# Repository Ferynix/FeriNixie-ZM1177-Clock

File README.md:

# FeriNixie ZM1177 Clock
 A compact nixie tube clock designed for six ZM1177s

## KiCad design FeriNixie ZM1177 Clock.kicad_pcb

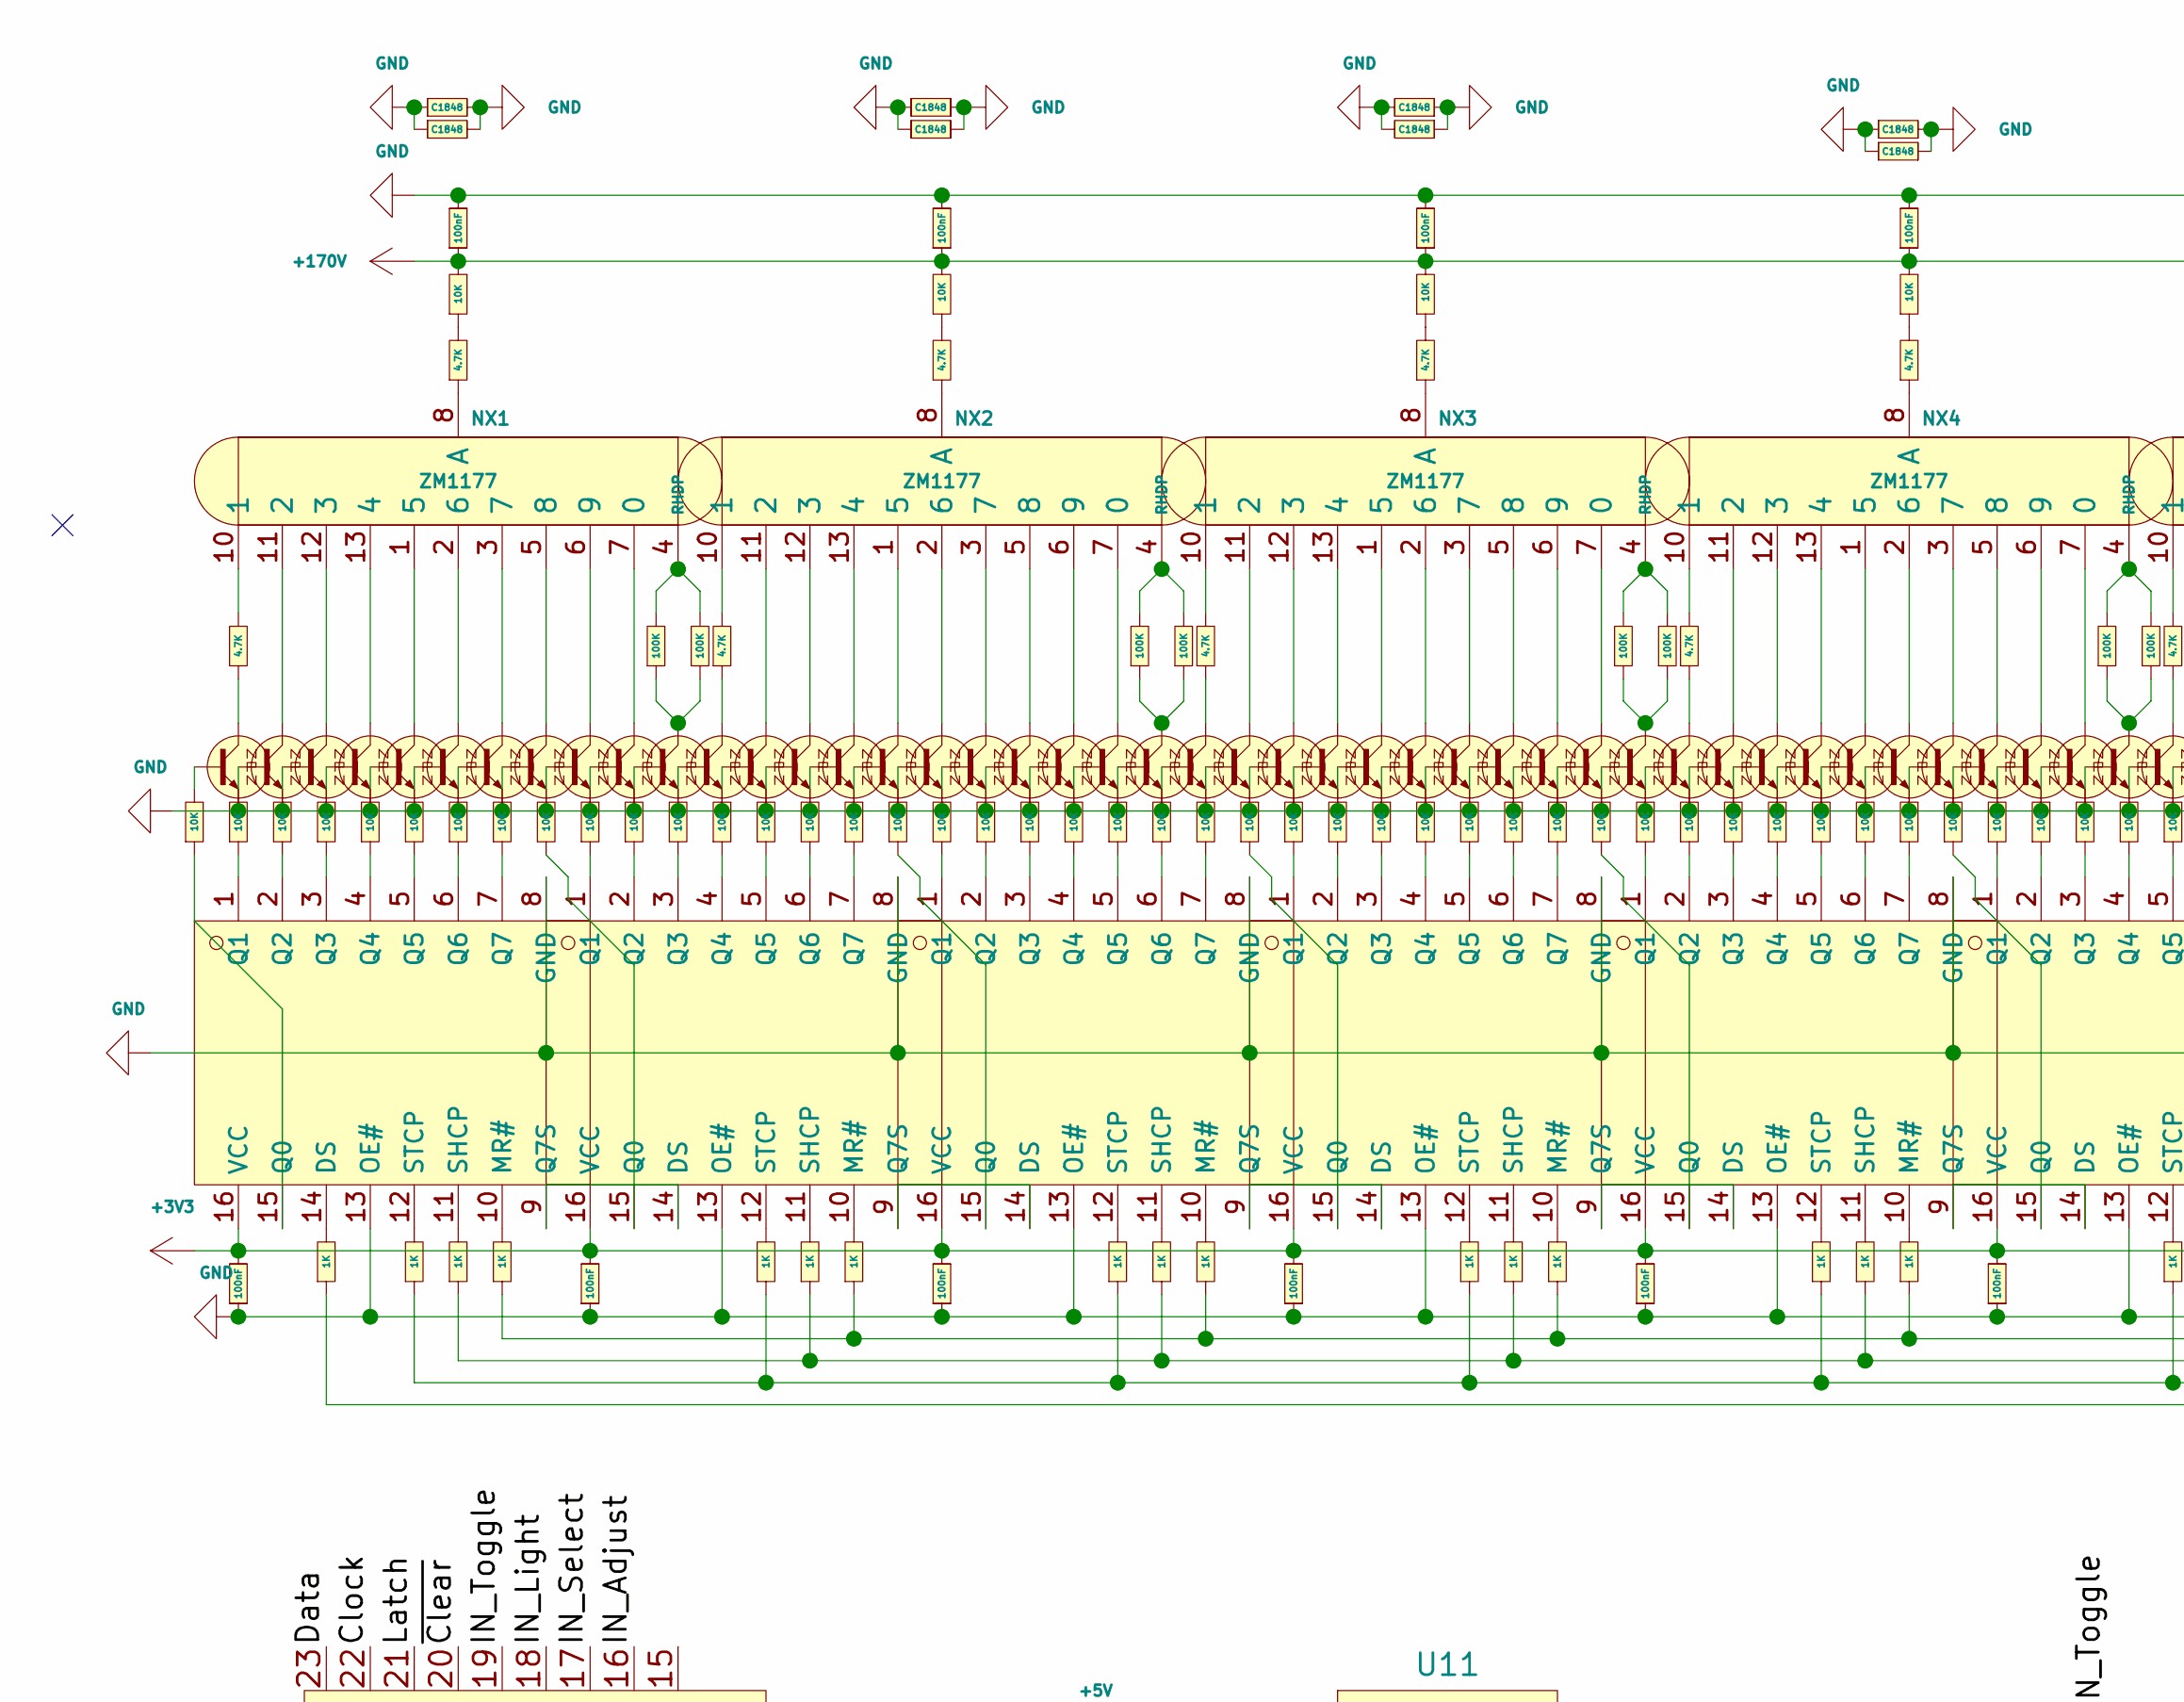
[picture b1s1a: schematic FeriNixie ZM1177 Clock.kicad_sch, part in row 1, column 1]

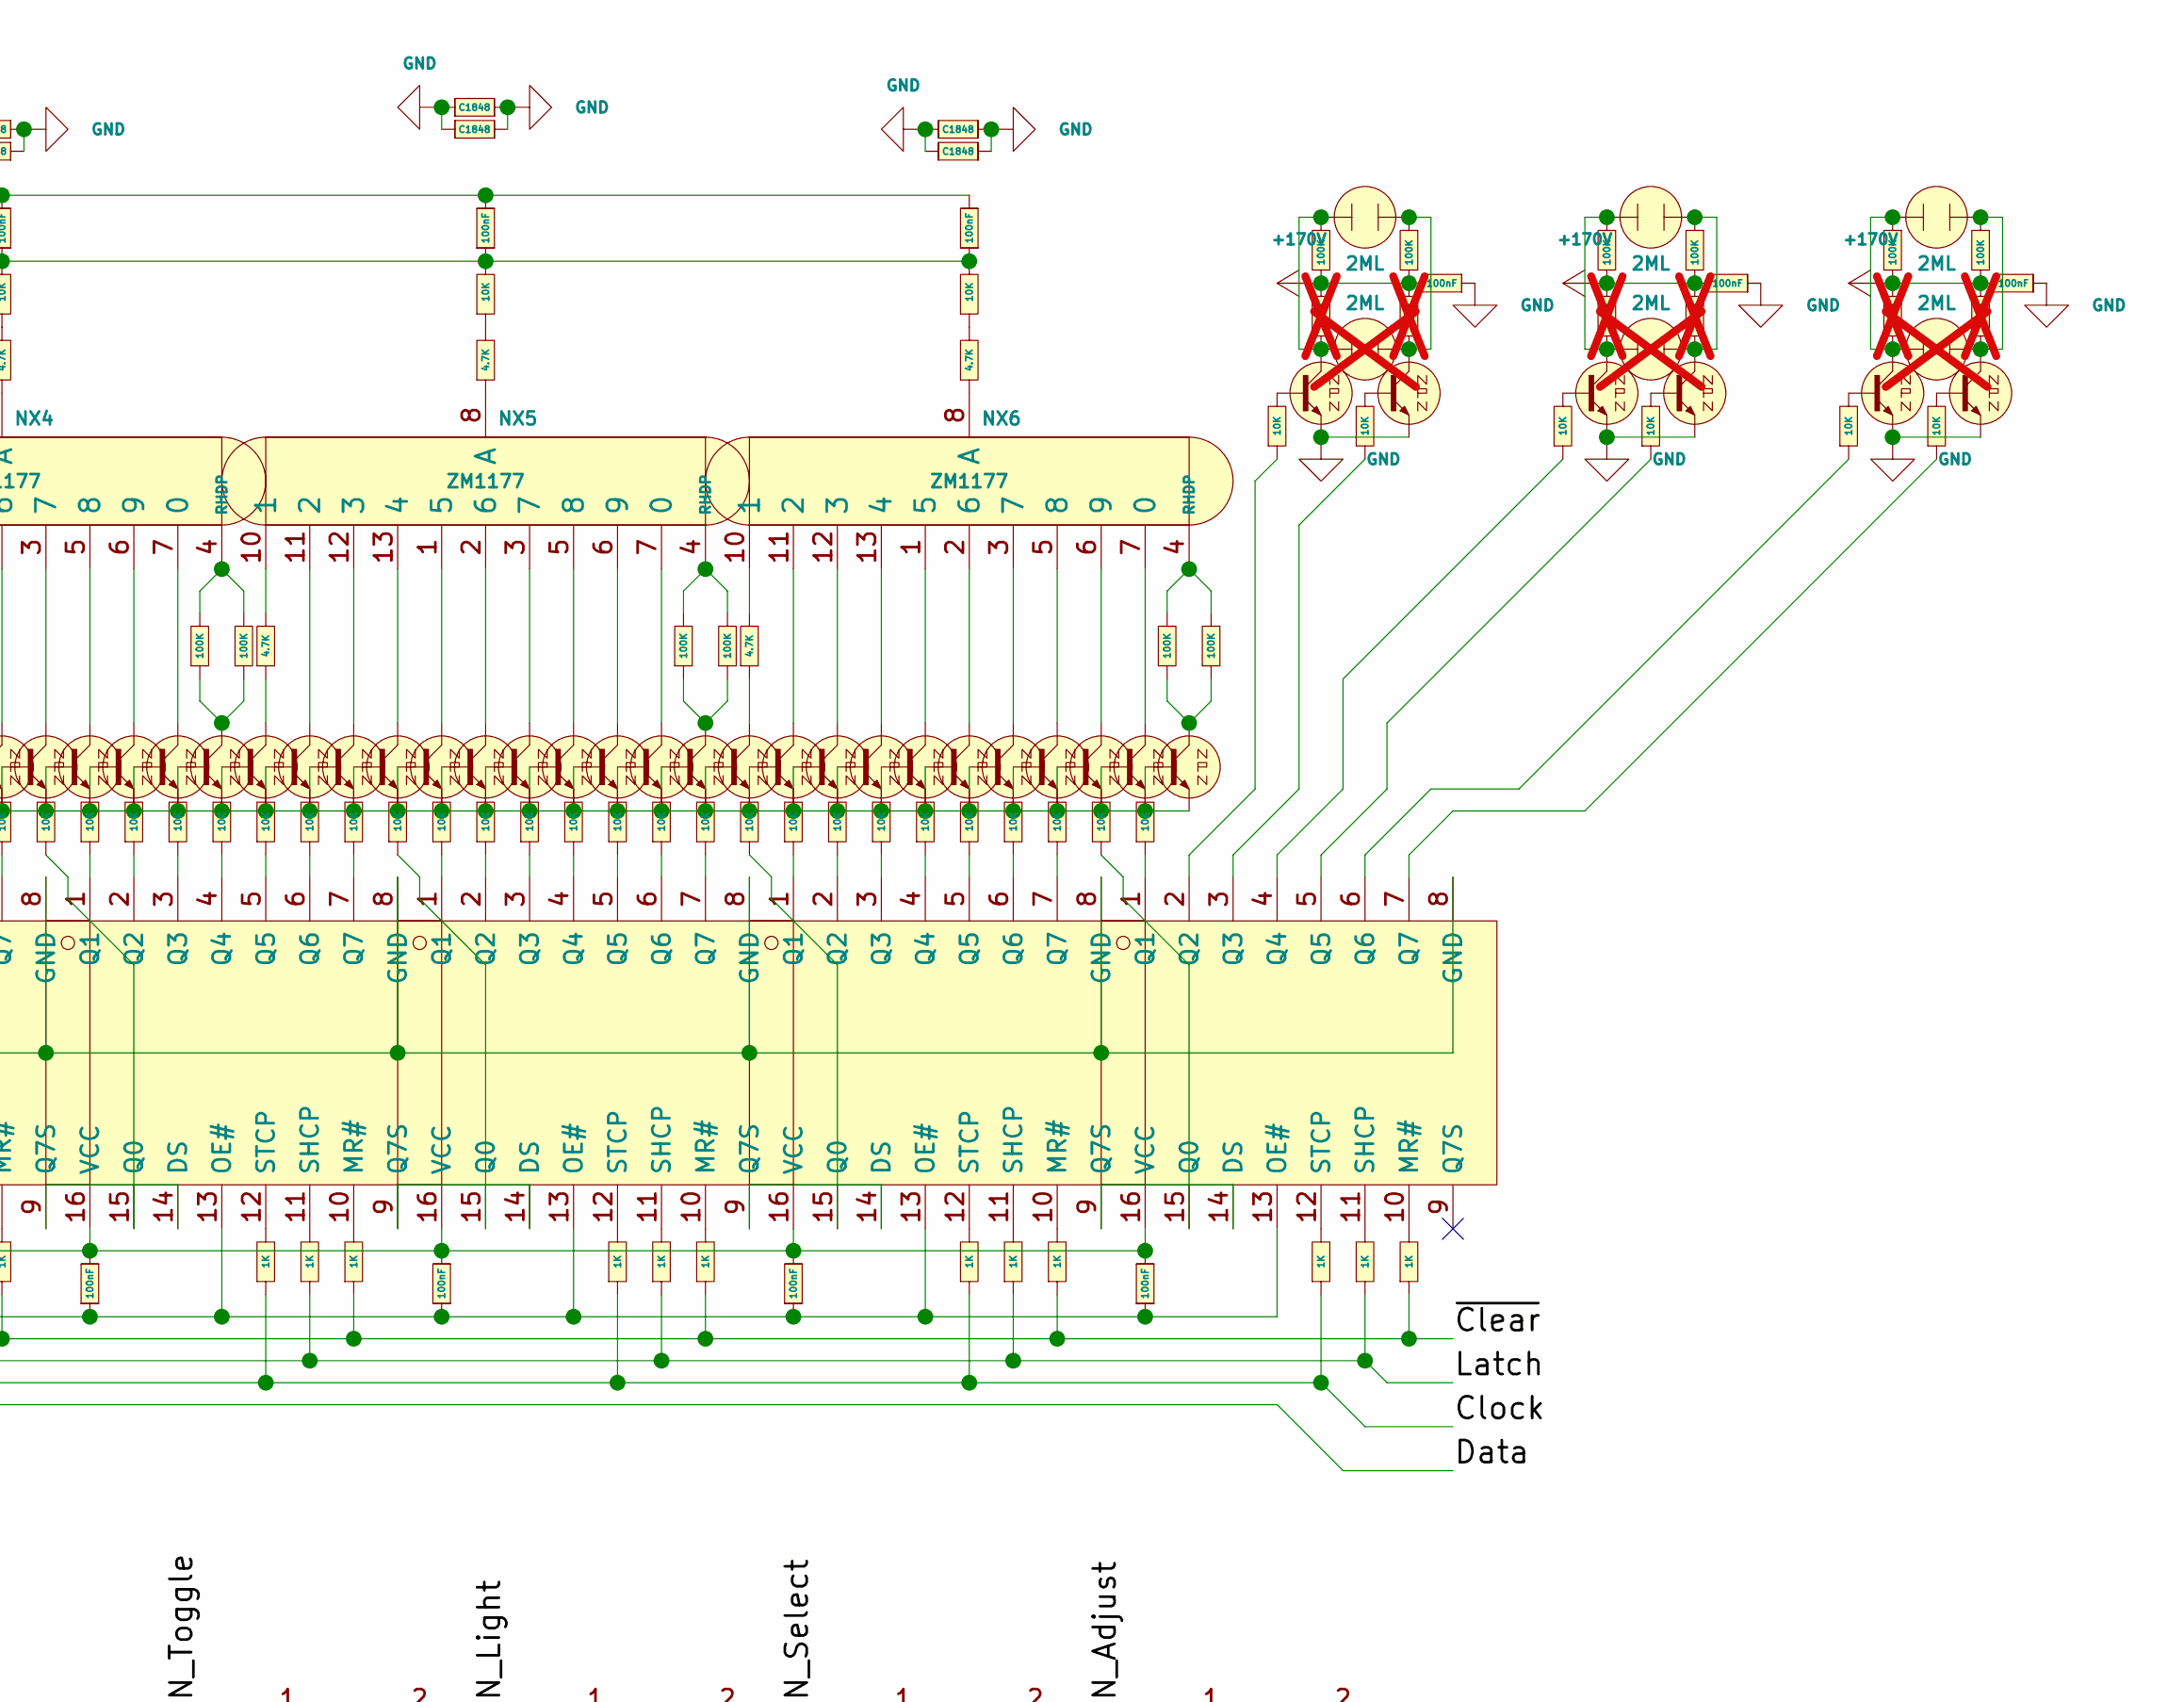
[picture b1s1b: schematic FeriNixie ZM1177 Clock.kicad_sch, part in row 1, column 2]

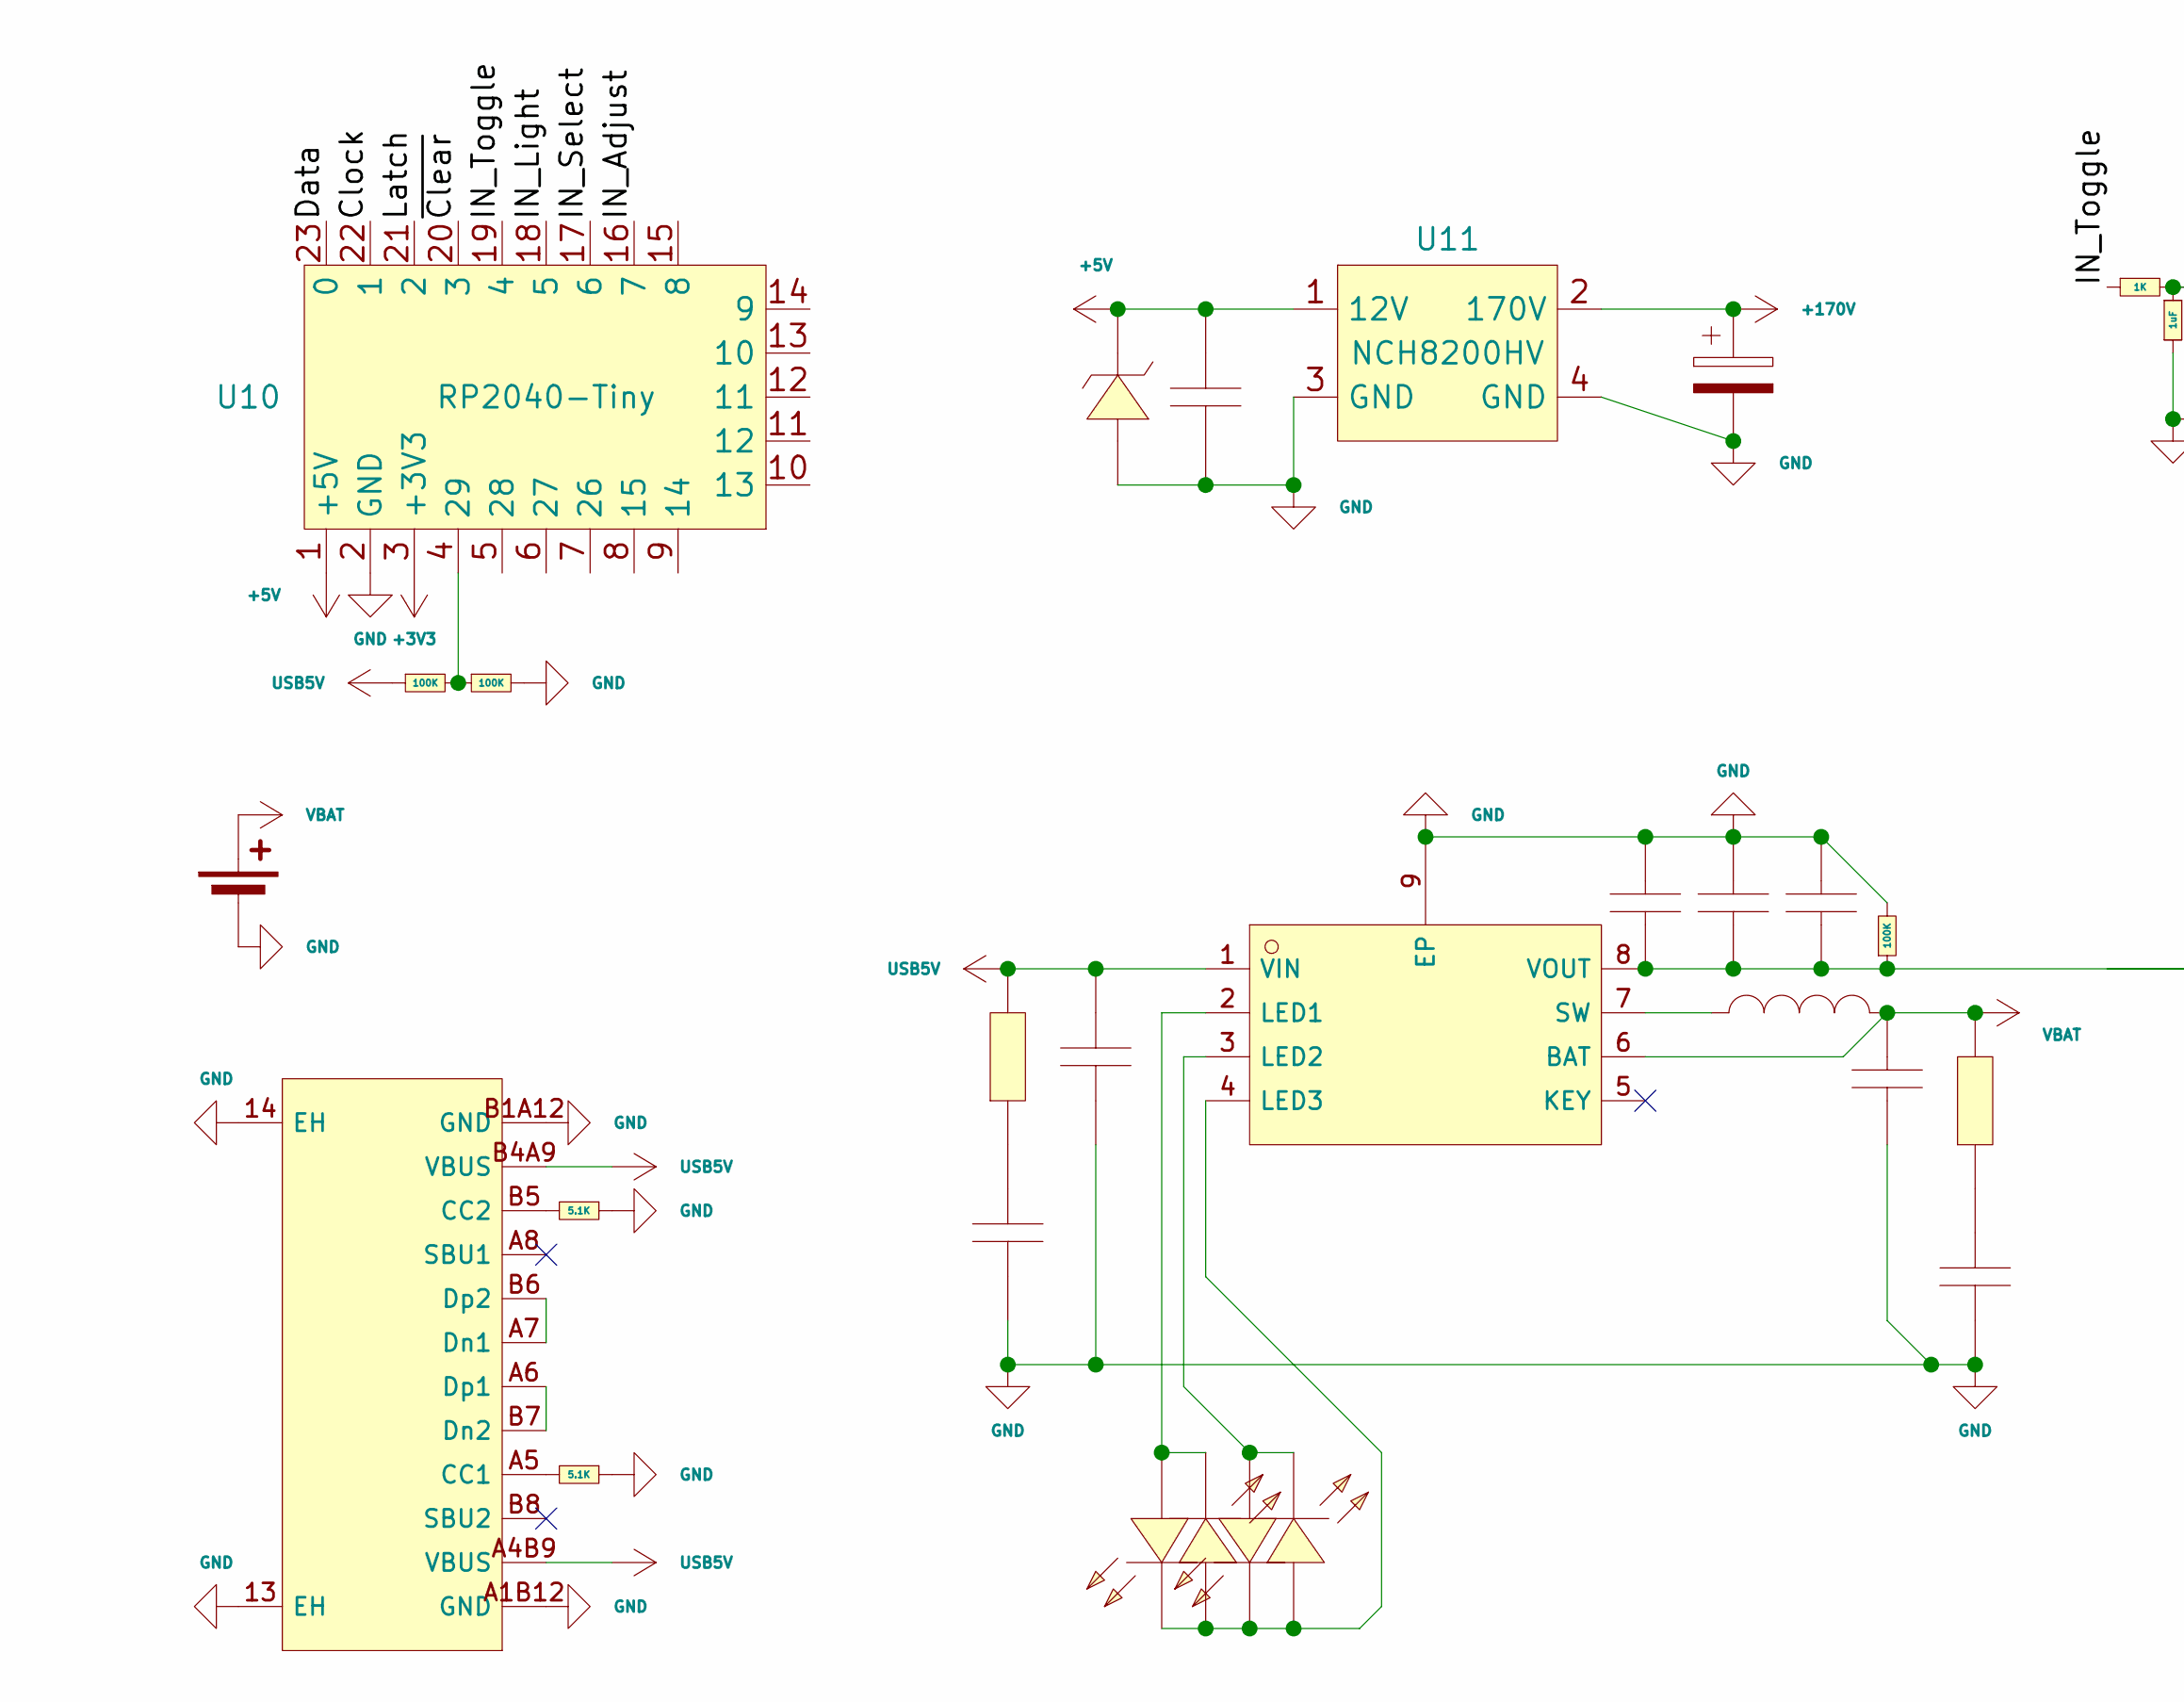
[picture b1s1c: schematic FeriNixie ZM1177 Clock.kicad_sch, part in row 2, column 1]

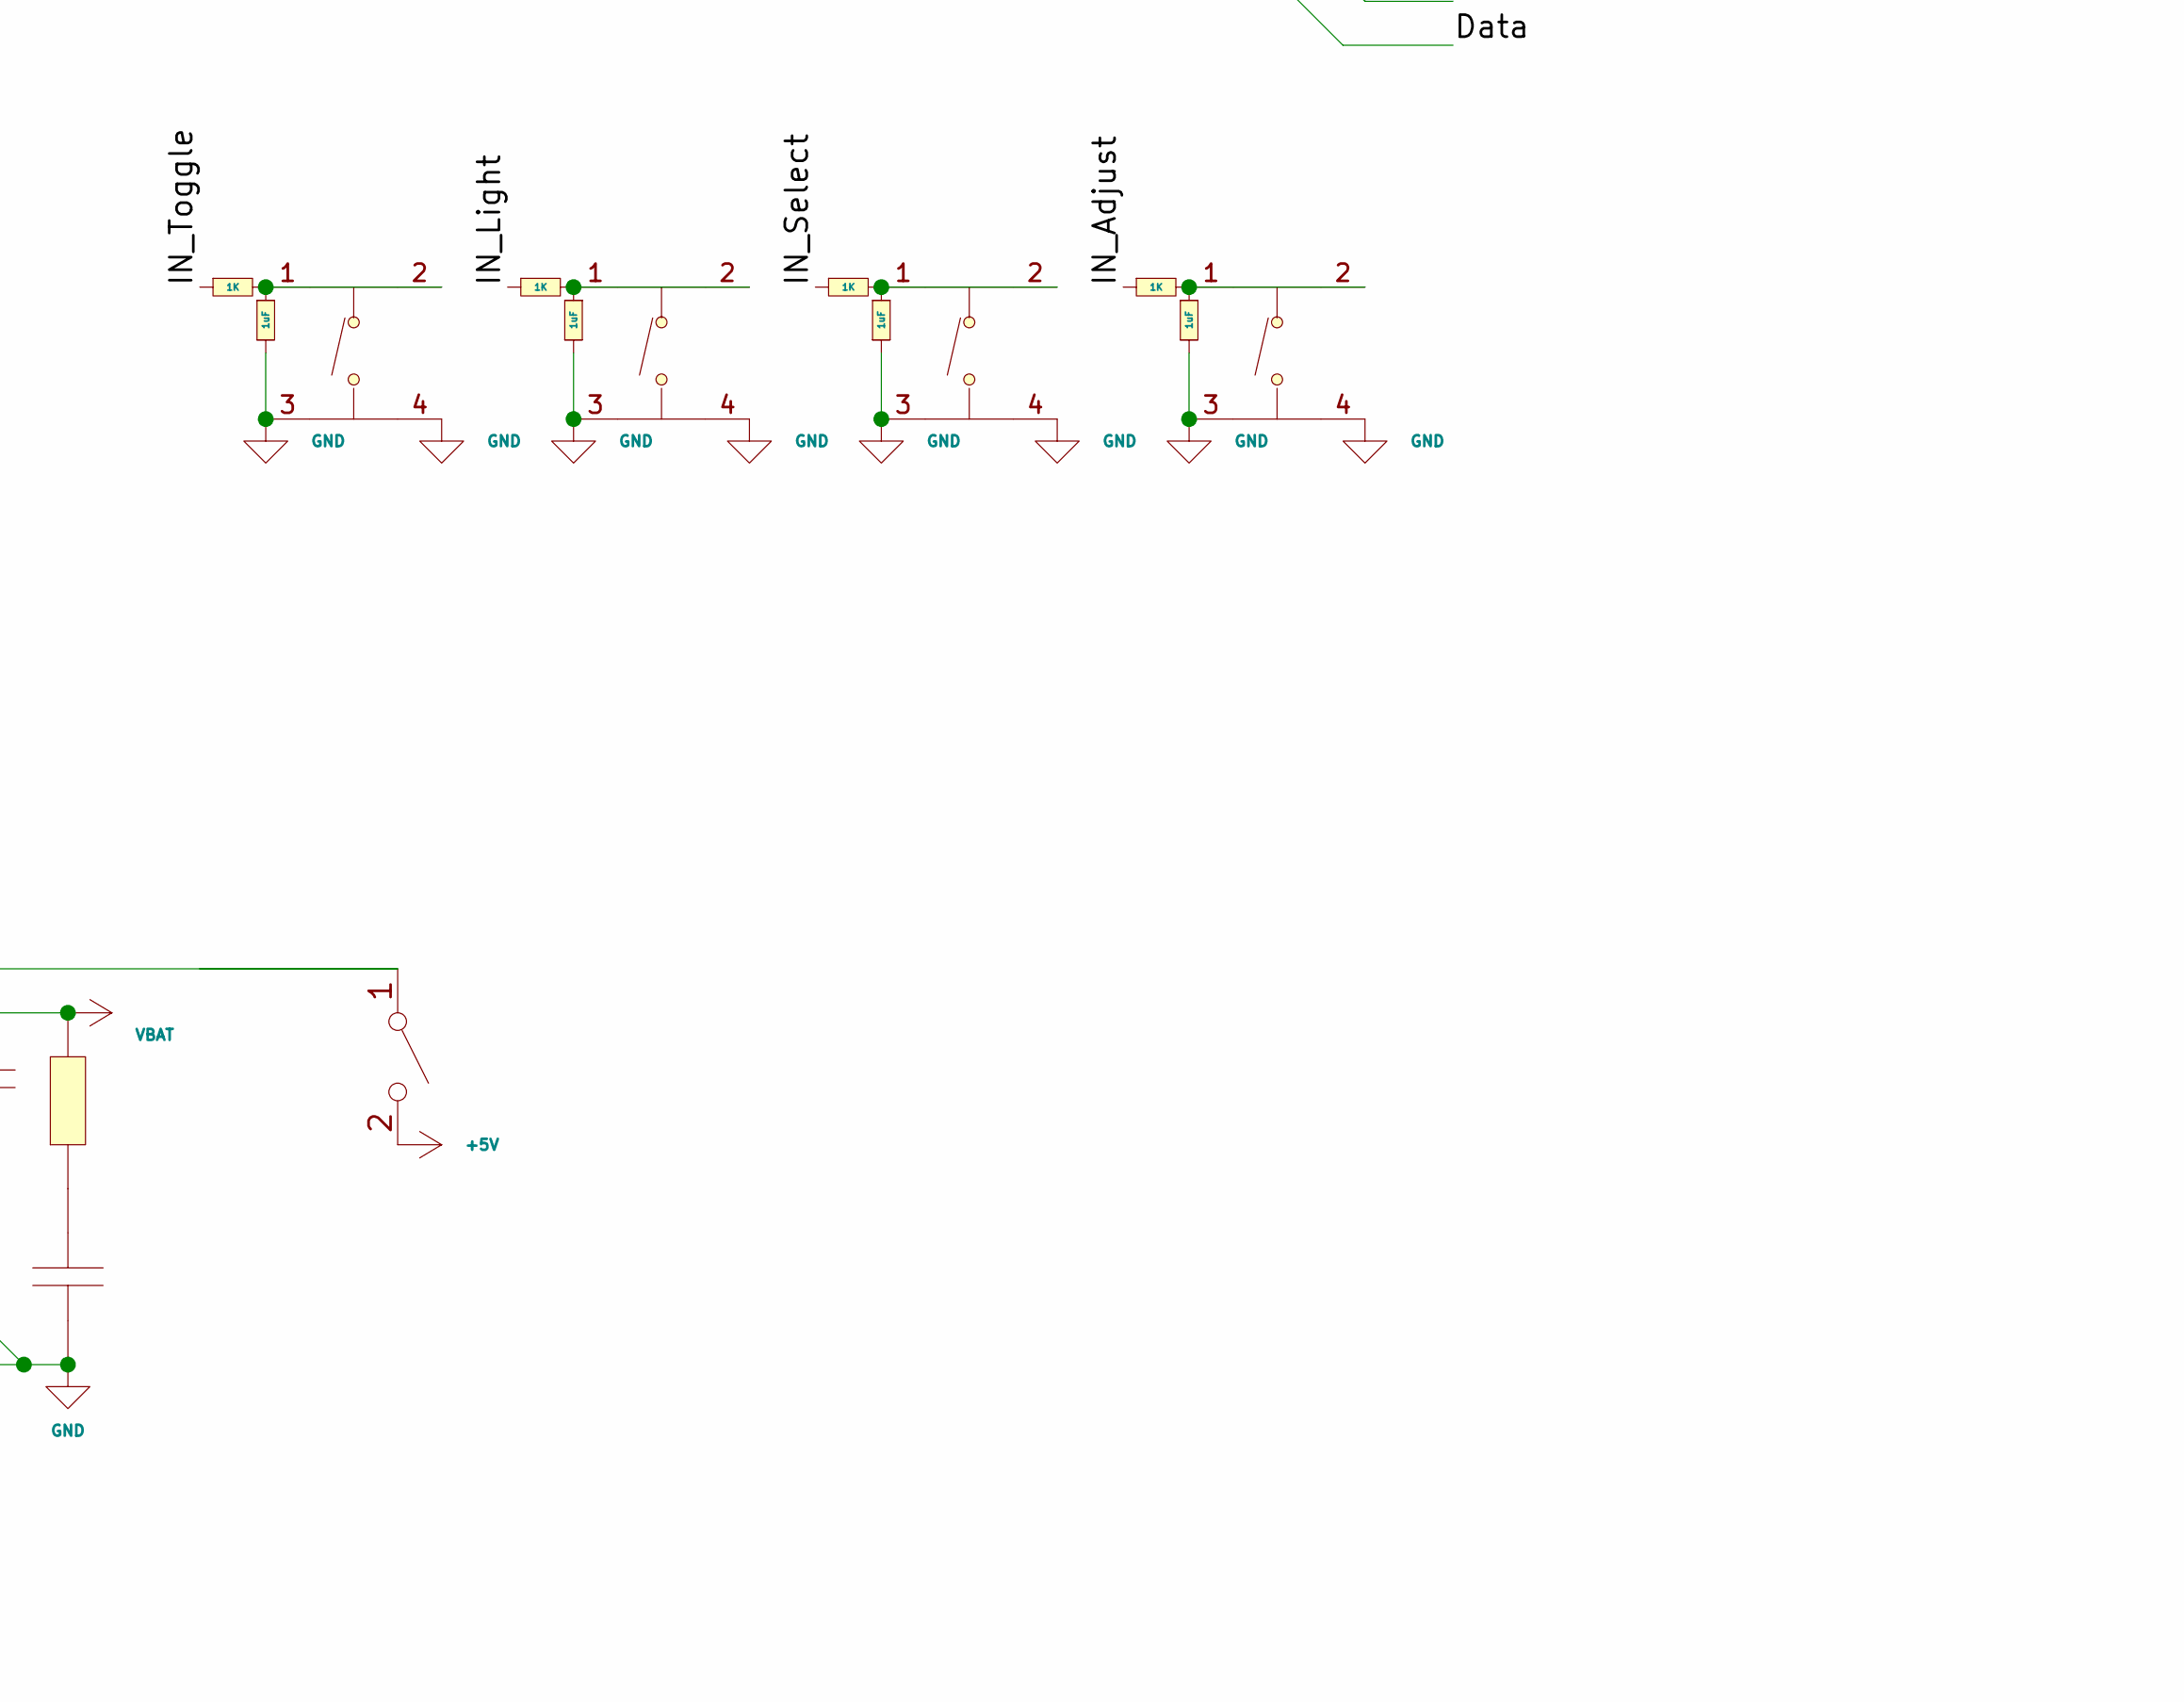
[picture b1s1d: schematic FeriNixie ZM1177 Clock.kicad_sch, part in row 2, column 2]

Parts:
BT1: Battery_Cell; BatteryHolder_Keystone_1042_1x18650
C1, C2, C3, C4, C5, C6, C7, C8, C43: 100nF; C_1206_3216Metric
C9, C10, C11, C12, C13, C14, C15, C16, C17: 100nF; C_0402_1005Metric
C18: C; C_Radial_D8.0mm_H11.5mm_P3.50mm
C19, C20, C21, C22, C23, C24, C25, C26, C27, C28, C29, C30: C1848
C31, C40, C41, C42: 1uF; R_0402_1005Metric
C32, C33, C37, C38: CL31A226KAHNNNE; C_1206_3216Metric; LCSC C12891
C34, C35, C36, C39: CL10A106KP8NNNC; C_0603_1608Metric; LCSC C19702
L1: FTM201610C1R0MCTA; L0806; LCSC C49211190
NE1, NE2, NE5: NeonIndicator_2ML_1MH_B10A
NE3, NE4, NE6: NeonIndicator_2ML_1MH_B10A; not fitted
NX1, NX2, NX3, NX4, NX5, NX6: NixieTube_ZM1177
Q1, Q2, Q3, Q4, Q5, Q6, Q7, Q8, Q9, Q10, Q11, Q12, Q13, Q14, Q15, Q16, Q17, Q18, Q19, Q20, Q21, Q22, Q23, Q24, Q25, Q26, Q27, Q28, Q29, Q30, Q31, Q32, Q33, Q34, Q35, Q36, Q37, Q38, Q39, Q40, Q41, Q42, Q43, Q44, Q45, Q46, Q47, Q48, Q49, Q50, Q51, Q52, Q53, Q54, Q55, Q56, Q57, Q58, Q59, Q60, Q61, Q62, Q63, Q64, Q65, Q66, Q67, Q68, Q69, Q70, Q71, Q72: C20069138; SOT-23-3_L2.9-W1.3-P1.90-LS2.4-BR
R1, R2, R3, R4, R5, R6: 10K; R_1206_3216Metric
R7, R9, R12, R14, R26, R27, R29, R30, R32, R33, R35, R36, R38, R39, R41, R42, R140, R146, R148, R150, R151: 100K; R_1206_3216Metric
R8, R10, R11, R13, R145, R149: 100K; R_1206_3216Metric; not fitted
R15, R16, R17, R18, R19, R20, R25, R28, R31, R34, R37, R40: 4.7K; R_1206_3216Metric
R21, R22, R23, R24, R43, R44, R45, R46, R47, R48, R49, R50, R51, R52, R53, R54, R55, R56, R57, R58, R59, R60, R61, R62, R63, R64, R65, R66, R67, R68, R69, R70, R71, R72, R73, R74, R75, R76, R77, R78, R79, R80, R81, R82, R83, R84, R85, R86, R87, R88, R89, R90, R91, R92, R93, R94, R95, R96, R97, R98, R99, R100, R101, R102, R103, R104, R105, R106, R107, R108, R137, R147: 10K; R_0402_1005Metric
R109, R110, R111, R112, R113, R114, R115, R116, R117, R118, R119, R120, R121, R122, R123, R124, R125, R126, R127, R128, R129, R130, R131, R132, R133, R134, R135, R136: 1K; R_0402_1005Metric
R138, R139: 0603WAF200KT5E; R_0603_1608Metric; LCSC C22977
R141, R142, R143, R144: 1K; C_0402_1005Metric
R254, R255: 5.1K; R_0402_1005Metric
SW1: SW_SPST; SW_SPST_L101011MS02Q
U1, U2, U3, U4, U5, U6, U7, U8, U9: 74HC595D,118; SOIC-16_L9.9-W3.9-P1.27-LS6.0-BL; LCSC C5947
U10: RP2040-Tiny; RP2040-Tiny Package Extra Clearance
U11: NCH8200HV; NCH8200HV Through-Hole
U12: 1SMA4740A_C19077479; SMA_L4.3-W2.6-LS5.0-RD; LCSC C19077479
U13: IP5306; ESOP-8_L4.9-W3.9-P1.27-LS6.0-BL-EP; LCSC C181692
U14: TYPE-C_16PIN_2MD(073); USB-C-SMD_TYPE-C-16PIN-2MD-073; LCSC C2765186
U15, U16, U17, U18: KT-0603R; LED-SMD_L1.6-W0.8-R-RD; LCSC C2286
U19, U20, U21, U22: TS-1187A-B-A-B; SW-SMD_4P-L5.1-W5.1-P3.70-LS6.5-TL_H1.5; LCSC C318884

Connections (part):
+3V3: C9.2, C10.2, C11.2, C12.2, C13.2, C14.2, C15.2, C16.2, C17.2, U1.16 (VCC), U2.16 (VCC), U3.16 (VCC), U4.16 (VCC), U5.16 (VCC), U6.16 (VCC), U7.16 (VCC), U8.16 (VCC), U9.16 (VCC), U10.3 (+3V3)
+5V: C39.2, SW1.2 (B), U10.1 (+5V), U11.1 (12V), U12.1 (K); also elsewhere on the board
+170V: C1.1, C2.1, C3.1, C4.1, C5.1, C6.1, C7.2, C8.2, C18.1, C43.2, R1.2, R2.2, R3.2, R4.2, R5.2, R6.2, R7.2, R8.2, R9.2, R10.2, R11.2, R12.2, R13.2, R14.2, R145.2, R146.2, R148.2, R149.2, U11.2 (170V)
/Clock: R110.1, R113.1, R116.1, R119.1, R122.1, R125.1, R128.1, R131.1, R134.1, U10.22 (1)
/Data: R109.1, U10.23 (0)
/IN_Adjust: R144.1, U10.16 (7)
/IN_Light: R142.1, U10.18 (5)
/IN_Select: R143.1, U10.17 (6)
/IN_Toggle: R141.1, U10.19 (4)
/Latch: R111.1, R114.1, R117.1, R120.1, R123.1, R126.1, R129.1, R132.1, R135.1, U10.21 (2)
/~Clear: R112.1, R115.1, R118.1, R121.1, R124.1, R127.1, R130.1, R133.1, R136.1, U10.20 (3)
GND: BT1.2 (-), C1.2, C2.2, C3.2, C4.2, C5.2, C6.2, C7.1, C8.1, C9.1, C10.1, C11.1, C12.1, C13.1, C14.1, C15.1, C16.1, C17.1, C18.2, C19.1, C19.2, C20.1, C20.2, C21.1, C21.2, C22.1, C22.2, C23.1, C23.2, C24.1, C24.2, C25.1, C25.2, C26.1, C26.2, C27.1, C27.2, C28.1, C28.2, C29.1, C29.2, C30.1, C30.2, C31.1, C32.1, C33.1, C34.1, C35.1, C36.1, C37.1, C38.1, C39.1, C40.1, C41.1, C42.1, C43.1, Q1.2 (E), Q2.2 (E), Q3.2 (E), Q4.2 (E), Q5.2 (E), Q6.2 (E), Q7.2 (E), Q8.2 (E), Q9.2 (E), Q10.2 (E), Q11.2 (E), Q12.2 (E), Q13.2 (E), Q14.2 (E), Q15.2 (E), Q16.2 (E), Q17.2 (E), Q18.2 (E), Q19.2 (E), Q20.2 (E), Q21.2 (E), Q22.2 (E), Q23.2 (E), Q24.2 (E), Q25.2 (E)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
unnamed: C34.2, R139.1
unnamed: C36.2, R138.1
unnamed: NE1.1 (A), NE3.2 (K), Q2.3 (C), R9.1, R10.1
unnamed: NE1.2 (K), NE3.1 (A), Q1.3 (C), R7.1, R8.1
unnamed: NE2.1 (A), NE4.2 (K), Q4.3 (C), R13.1, R14.1
unnamed: NE2.2 (K), NE4.1 (A), Q3.3 (C), R11.1, R12.1
unnamed: NE5.1 (A), NE6.2 (K), Q72.3 (C), R148.1, R149.1
unnamed: NE5.2 (K), NE6.1 (A), Q71.3 (C), R145.1, R146.1
unnamed: NX1.7 (0), Q14.3 (C)
unnamed: NX1.10 (1), R25.2
unnamed: NX1.11 (2), Q6.3 (C)
unnamed: NX1.12 (3), Q7.3 (C)
unnamed: NX1.13 (4), Q8.3 (C)
unnamed: NX1.1 (5), Q9.3 (C)
unnamed: NX1.2 (6), Q10.3 (C)
unnamed: NX1.3 (7), Q11.3 (C)
unnamed: NX1.5 (8), Q12.3 (C)
unnamed: NX1.6 (9), Q13.3 (C)
unnamed: NX1.8 (A), R15.1
unnamed: NX1.4 (RHDP), R26.2, R27.2
unnamed: NX2.7 (0), Q25.3 (C)
unnamed: NX2.10 (1), R28.2
unnamed: NX2.11 (2), Q17.3 (C)
unnamed: NX2.12 (3), Q18.3 (C)
unnamed: NX2.13 (4), Q19.3 (C)
unnamed: NX2.1 (5), Q20.3 (C)
unnamed: NX2.2 (6), Q21.3 (C)
unnamed: NX2.3 (7), Q22.3 (C)
unnamed: NX2.5 (8), Q23.3 (C)
unnamed: NX2.6 (9), Q24.3 (C)
unnamed: NX2.8 (A), R16.1
unnamed: NX2.4 (RHDP), R29.2, R30.2
unnamed: NX3.7 (0), Q36.3 (C)
unnamed: NX3.10 (1), R31.2
unnamed: NX3.11 (2), Q28.3 (C)
unnamed: NX3.12 (3), Q29.3 (C)
unnamed: NX3.13 (4), Q30.3 (C)
unnamed: NX3.1 (5), Q31.3 (C)
unnamed: NX3.2 (6), Q32.3 (C)
unnamed: NX3.3 (7), Q33.3 (C)
unnamed: NX3.5 (8), Q34.3 (C)
unnamed: NX3.6 (9), Q35.3 (C)
unnamed: NX3.8 (A), R17.1
unnamed: NX3.4 (RHDP), R32.2, R33.2
unnamed: NX4.7 (0), Q47.3 (C)
unnamed: NX4.10 (1), R34.2
unnamed: NX4.11 (2), Q39.3 (C)
unnamed: NX4.12 (3), Q40.3 (C)
unnamed: NX4.13 (4), Q41.3 (C)
unnamed: NX4.1 (5), Q42.3 (C)
unnamed: NX4.2 (6), Q43.3 (C)
unnamed: NX4.3 (7), Q44.3 (C)
unnamed: NX4.5 (8), Q45.3 (C)
unnamed: NX4.6 (9), Q46.3 (C)
unnamed: NX4.8 (A), R18.1
unnamed: NX4.4 (RHDP), R35.2, R36.2
unnamed: NX5.7 (0), Q58.3 (C)
unnamed: NX5.10 (1), R37.2
unnamed: NX5.11 (2), Q50.3 (C)
unnamed: NX5.12 (3), Q51.3 (C)
unnamed: NX5.13 (4), Q52.3 (C)
unnamed: NX5.1 (5), Q53.3 (C)
unnamed: NX5.2 (6), Q54.3 (C)
unnamed: NX5.3 (7), Q55.3 (C)
unnamed: NX5.5 (8), Q56.3 (C)
unnamed: NX5.6 (9), Q57.3 (C)
unnamed: NX5.8 (A), R19.1
unnamed: NX5.4 (RHDP), R38.2, R39.2
unnamed: NX6.7 (0), Q69.3 (C)
unnamed: NX6.10 (1), R40.2
unnamed: NX6.11 (2), Q61.3 (C)
unnamed: NX6.12 (3), Q62.3 (C)
unnamed: NX6.13 (4), Q63.3 (C)
unnamed: NX6.1 (5), Q64.3 (C)
unnamed: NX6.2 (6), Q65.3 (C)
unnamed: NX6.3 (7), Q66.3 (C)
unnamed: NX6.5 (8), Q67.3 (C)
unnamed: NX6.6 (9), Q68.3 (C)
unnamed: NX6.8 (A), R20.1
unnamed: NX6.4 (RHDP), R41.2, R42.2
unnamed: Q1.1 (B), R21.2
unnamed: Q2.1 (B), R22.2
unnamed: Q3.1 (B), R23.2
unnamed: Q4.1 (B), R24.2
unnamed: Q5.1 (B), R43.2
unnamed: Q5.3 (C), R25.1
unnamed: Q6.1 (B), R44.2
unnamed: Q7.1 (B), R45.2
unnamed: Q8.1 (B), R46.2
unnamed: Q9.1 (B), R47.2
unnamed: Q10.1 (B), R48.2
unnamed: Q11.1 (B), R49.2
unnamed: Q12.1 (B), R50.2
unnamed: Q13.1 (B), R51.2
unnamed: Q14.1 (B), R52.2
unnamed: Q15.1 (B), R53.2
unnamed: Q15.3 (C), R26.1, R27.1
unnamed: Q16.1 (B), R54.2
unnamed: Q16.3 (C), R28.1
unnamed: Q17.1 (B), R55.2
unnamed: Q18.1 (B), R56.2
unnamed: Q19.1 (B), R57.2
unnamed: Q20.1 (B), R58.2
unnamed: Q21.1 (B), R59.2
unnamed: Q22.1 (B), R60.2
unnamed: Q23.1 (B), R61.2
unnamed: Q24.1 (B), R62.2
unnamed: Q25.1 (B), R63.2
unnamed: Q26.1 (B), R64.2
unnamed: Q26.3 (C), R29.1, R30.1
unnamed: Q27.1 (B), R65.2
unnamed: Q27.3 (C), R31.1
unnamed: Q28.1 (B), R66.2
unnamed: Q29.1 (B), R67.2
unnamed: Q30.1 (B), R68.2
unnamed: Q31.1 (B), R69.2
unnamed: Q32.1 (B), R70.2
unnamed: Q33.1 (B), R71.2
unnamed: Q34.1 (B), R72.2
unnamed: Q35.1 (B), R73.2
unnamed: Q36.1 (B), R74.2
unnamed: Q37.1 (B), R75.2
unnamed: Q37.3 (C), R32.1, R33.1
unnamed: Q38.1 (B), R76.2
unnamed: Q38.3 (C), R34.1
unnamed: Q39.1 (B), R77.2
unnamed: Q40.1 (B), R78.2
unnamed: Q41.1 (B), R79.2
unnamed: Q42.1 (B), R80.2
unnamed: Q43.1 (B), R81.2
unnamed: Q44.1 (B), R82.2
unnamed: Q45.1 (B), R83.2
unnamed: Q46.1 (B), R84.2
unnamed: Q47.1 (B), R85.2
unnamed: Q48.1 (B), R86.2
unnamed: Q48.3 (C), R35.1, R36.1
unnamed: Q49.1 (B), R87.2
unnamed: Q49.3 (C), R37.1
unnamed: Q50.1 (B), R88.2
unnamed: Q51.1 (B), R89.2
unnamed: Q52.1 (B), R90.2
unnamed: Q53.1 (B), R91.2
unnamed: Q54.1 (B), R92.2
unnamed: Q55.1 (B), R93.2
unnamed: Q56.1 (B), R94.2
unnamed: Q57.1 (B), R95.2
unnamed: Q58.1 (B), R96.2
unnamed: Q59.1 (B), R97.2
unnamed: Q59.3 (C), R38.1, R39.1
unnamed: Q60.1 (B), R98.2
unnamed: Q60.3 (C), R40.1
unnamed: Q61.1 (B), R99.2
unnamed: Q62.1 (B), R100.2
unnamed: Q63.1 (B), R101.2
unnamed: Q64.1 (B), R102.2
unnamed: Q65.1 (B), R103.2
unnamed: Q66.1 (B), R104.2
unnamed: Q67.1 (B), R105.2
unnamed: Q68.1 (B), R106.2
unnamed: Q69.1 (B), R107.2
unnamed: Q70.1 (B), R108.2
unnamed: Q70.3 (C), R41.1, R42.1
unnamed: Q71.1 (B), R137.2
unnamed: Q72.1 (B), R147.2
unnamed: R1.1, R15.2
unnamed: R2.1, R16.2
unnamed: R3.1, R17.2
unnamed: R4.1, R18.2
unnamed: R5.1, R19.2
unnamed: R6.1, R20.2
unnamed 182: C33.2, C37.2, C38.2, R140.1, SW1.1 (A), U13.8 (VOUT); also elsewhere on the board
unnamed: R109.2, U1.14 (DS)
unnamed: R112.2, U1.10 (MR#)
unnamed: R43.1, U1.15 (Q0)
unnamed: R44.1, U1.1 (Q1)
unnamed: R45.1, U1.2 (Q2)
unnamed: R46.1, U1.3 (Q3)
unnamed: R47.1, U1.4 (Q4)
unnamed: R48.1, U1.5 (Q5)
unnamed: R49.1, U1.6 (Q6)
unnamed: R50.1, U1.7 (Q7)
unnamed: U1.9 (Q7S), U2.14 (DS)
unnamed: R111.2, U1.11 (SHCP)
unnamed: R110.2, U1.12 (STCP)
unnamed: R115.2, U2.10 (MR#)
unnamed: R51.1, U2.15 (Q0)
unnamed: R52.1, U2.1 (Q1)
unnamed: R53.1, U2.2 (Q2)
unnamed: R54.1, U2.3 (Q3)
unnamed: R55.1, U2.4 (Q4)
unnamed: R56.1, U2.5 (Q5)
unnamed: R57.1, U2.6 (Q6)
unnamed: R58.1, U2.7 (Q7)
unnamed: U2.9 (Q7S), U3.14 (DS)
unnamed: R114.2, U2.11 (SHCP)
unnamed: R113.2, U2.12 (STCP)
unnamed: R118.2, U3.10 (MR#)
unnamed: R59.1, U3.15 (Q0)
unnamed: R60.1, U3.1 (Q1)
unnamed: R61.1, U3.2 (Q2)
unnamed: R62.1, U3.3 (Q3)
unnamed: R63.1, U3.4 (Q4)
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
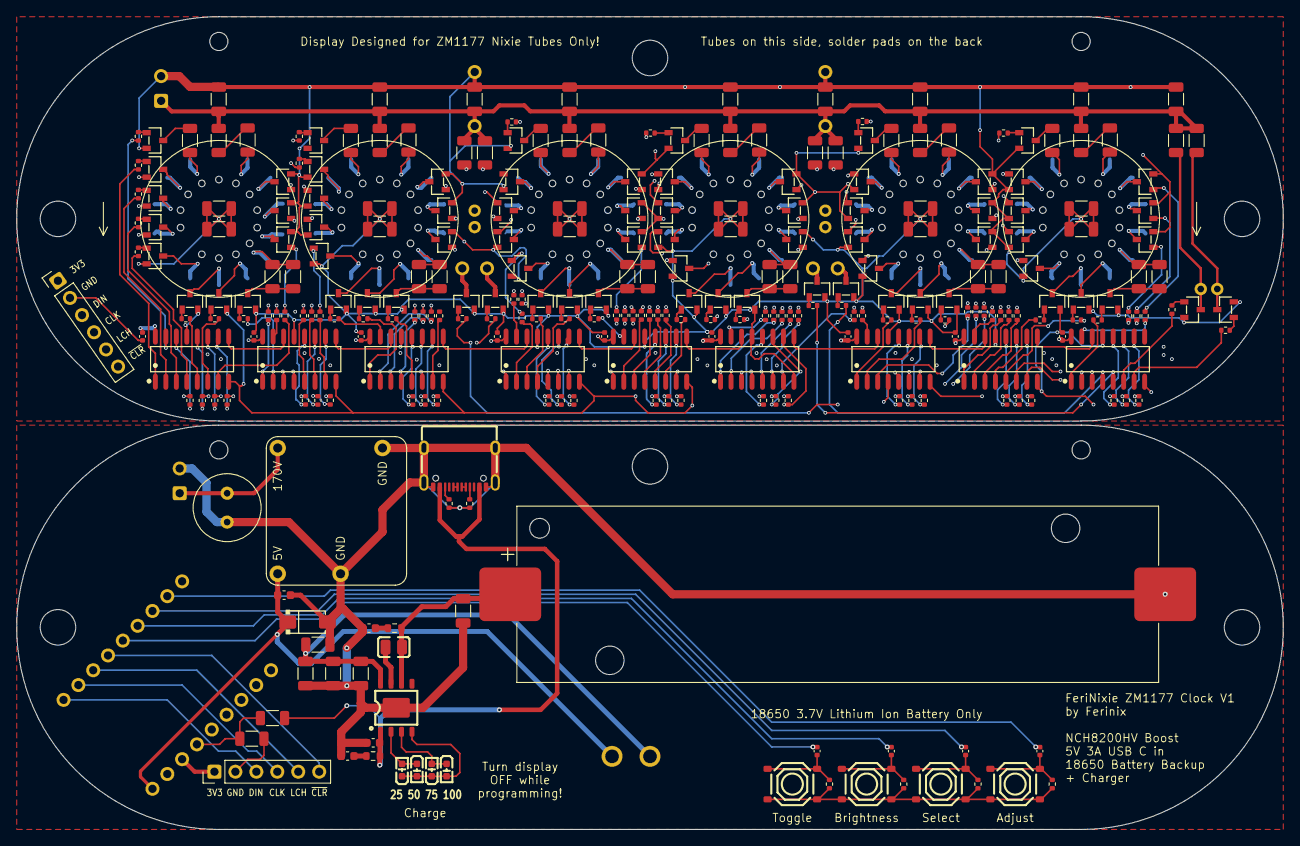
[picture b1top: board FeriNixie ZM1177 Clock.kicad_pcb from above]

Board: 4 copper layers, 153.5 x 98.5 mm, 296 parts (0 on the bottom side), 306 nets.

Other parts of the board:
SW: L101011MS02Q; SW_SPST_L101011MS02Q

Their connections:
+5V: SW.1; also elsewhere on the board
unnamed 182: SW.2; also elsewhere on the board
